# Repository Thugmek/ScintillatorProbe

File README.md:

# Scintillator Gamma Detector

## License

All software in this repository is licensed under [GNU GPLv3](https://choosealicense.com/licenses/gpl-3.0/).
All hardware in this repository is licensed under [CERN OHL v2 Permissive](https://choosealicense.com/licenses/cern-ohl-p-2.0/).

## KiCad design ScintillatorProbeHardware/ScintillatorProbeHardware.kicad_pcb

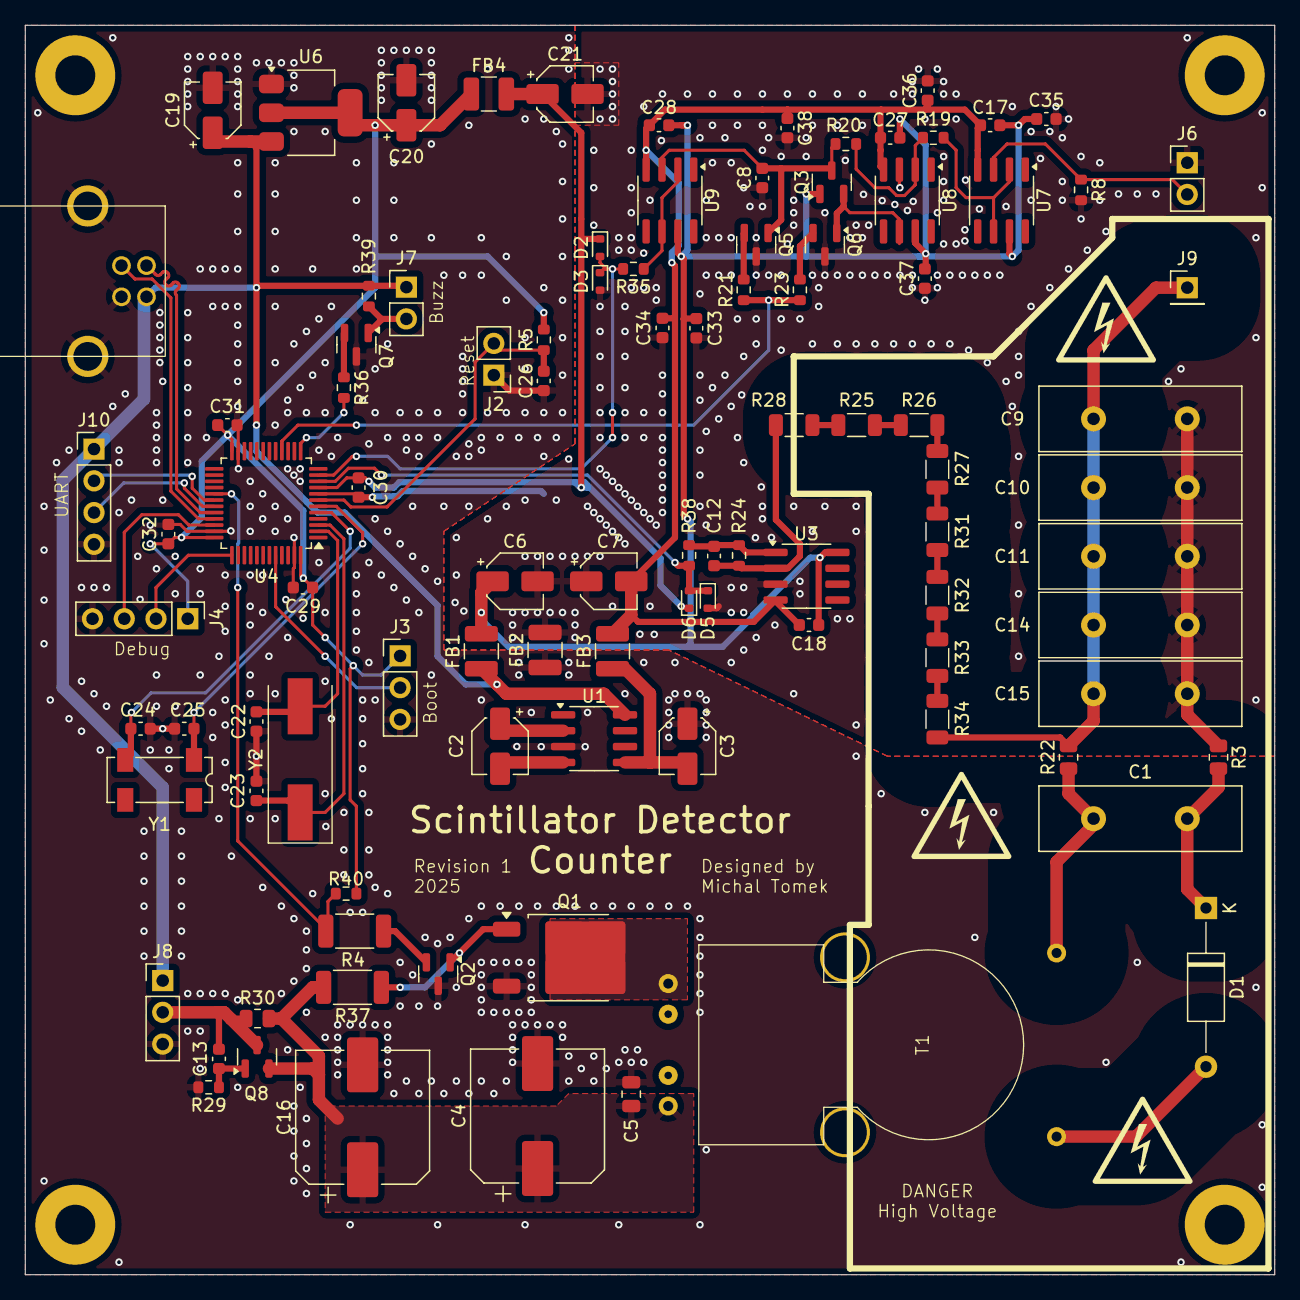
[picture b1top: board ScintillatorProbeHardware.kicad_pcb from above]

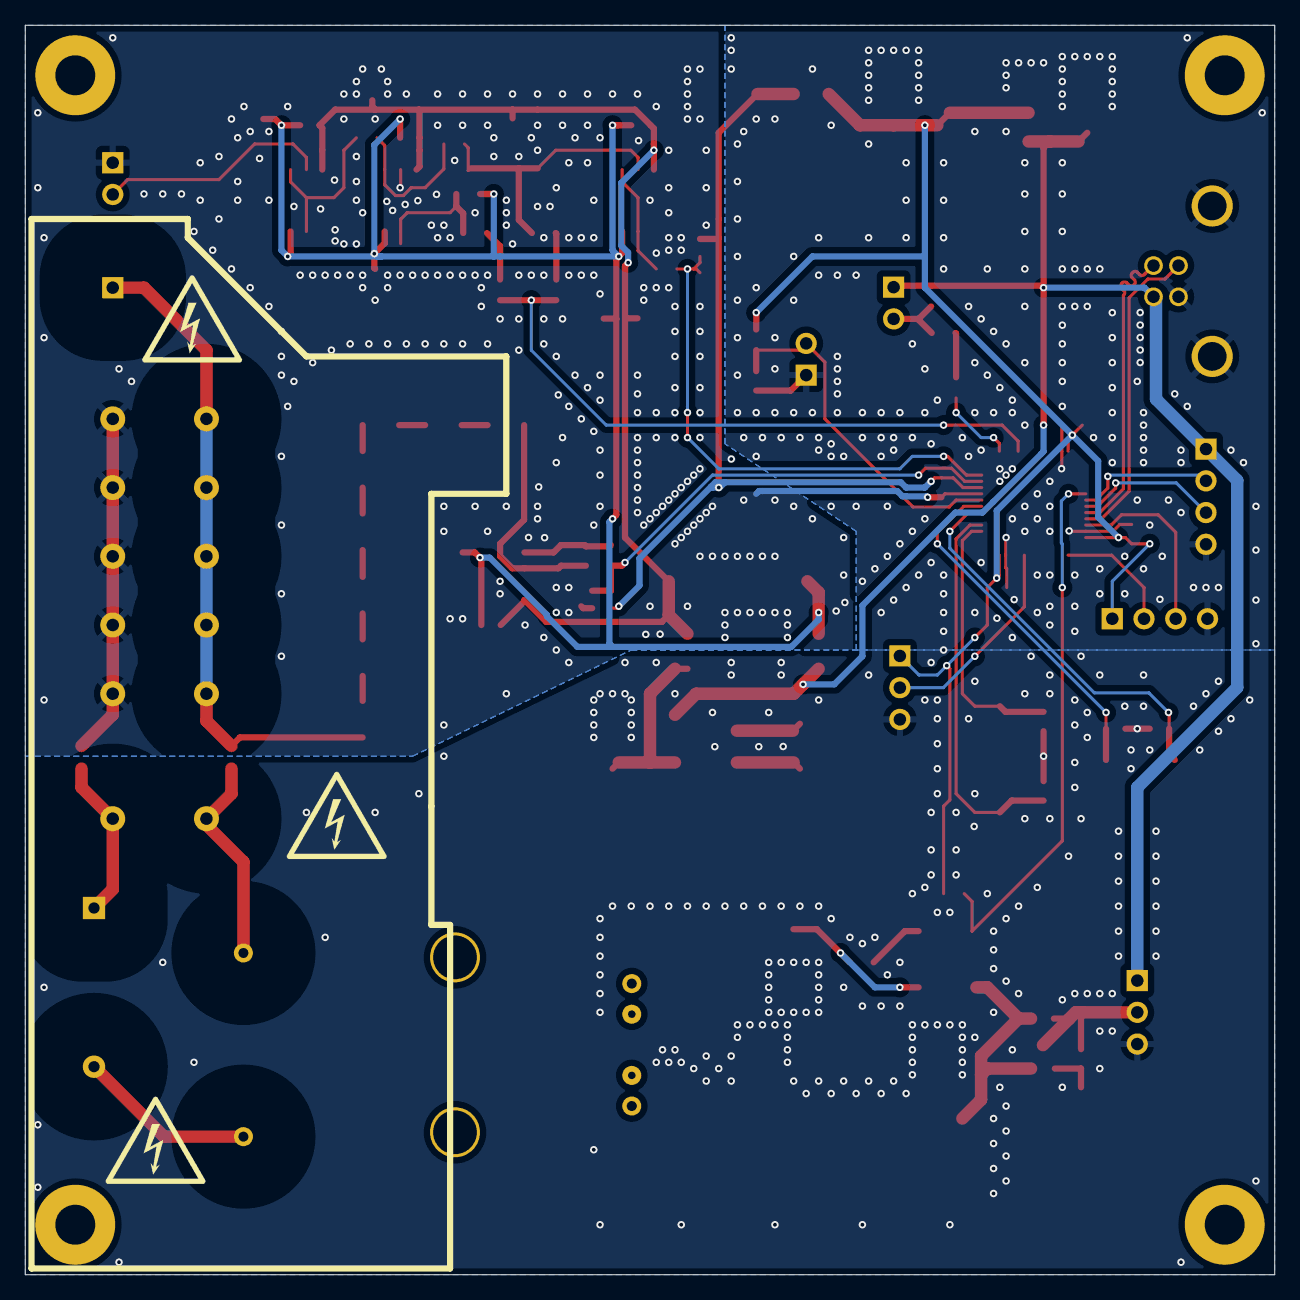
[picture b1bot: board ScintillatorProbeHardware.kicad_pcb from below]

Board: 2 copper layers, 100.0 x 100.0 mm, 109 parts (3 on the bottom side), 56 nets.

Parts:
C1: 10n/3000V; C_Disc_D16.0mm_W5.0mm_P7.50mm
C2, C3, C6, C7, C19, C20, C21: 10u; CP_Elec_4x5.4
C4, C16: 1000u; CP_Elec_10x10.5
C5: 10u; C_0805_2012Metric
C8: 10n; C_0603_1608Metric
C9, C10, C11, C14, C15: 10n; C_Disc_D16.0mm_W5.0mm_P7.50mm
C12, C18, C26: 100n; C_0603_1608Metric
C13, C17, C27, C28, C29, C30, C31, C32, C33, C34, C35, C36, C37, C38: 1u; C_0603_1608Metric
C22, C23, C24, C25: 20p; C_0603_1608Metric
D1: 2CL71A; D_A-405_P12.70mm_Horizontal
D2, D3, D5, D6: D_Schottky; D_SOD-523
FB1, FB2, FB3, FB4: 620Ω@1MHz; L_1210_3225Metric
H1, H2, H3, H4: MountingHole; MountingHole_3.2mm_M3_Pad
J1: USB_B; Amphenol_USB_B
J2, J7: Conn_01x02; PinHeader_1x02_P2.54mm_Vertical
J3, J8: Conn_01x03; PinHeader_1x03_P2.54mm_Vertical
J4, J10: Conn_01x04; PinHeader_1x04_P2.54mm_Vertical
J6: PinHeader_1x02_P2.54mm_Vertical
J9: Conn_01x01; PinHeader_1x01_P2.54mm_Vertical
Q1: 15N10; TO-252-2
Q2, Q3, Q5, Q6, Q7: S8050; SOT-23
Q8: MDD2302; SOT-23
R3, R22: 47k; R_0805_2012Metric
R4, R37: 330R; R_2010_5025Metric
R5, R20: 10k; R_0603_1608Metric
R8, R19, R35, R36, R38, R39, R40: 1k; R_0603_1608Metric
R21, R23: 330R; R_0603_1608Metric
R24: 9k1; R_0603_1608Metric
R25, R26, R27, R28, R31, R32, R33, R34: 1M; R_1206_3216Metric
R29: 100k; R_0603_1608Metric
R30: 47R; R_0805_2012Metric
SYM1, SYM2, SYM3, SYM4, SYM5, SYM6: SYM_Flash_Small; W012 - electricity hazard
T1: 24:1800; 15kV_Transformer
U1: ICL7660; SOIC-8_3.9x4.9mm_P1.27mm
U3: LM358; SOIC-8_3.9x4.9mm_P1.27mm
U4: STM32F103C8Tx; LQFP-48_7x7mm_P0.5mm
U6: AMS1117-3.3; SOT-223-3_TabPin2
U7, U8, U9: LM318N; SOIC-8_3.9x4.9mm_P1.27mm
Y1: 32.768kHz; Crystal_SMD_SeikoEpson_MC306-4Pin_8.0x3.2mm
Y2: 8MHz; Crystal_SMD_HC49-SD

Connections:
+3.3V: C20.1, C29.2, C31.2, C32.2, FB4.1, J3.1, J4.1, R5.2, R40.1, U4.24 (VDD), U4.36 (VDD), U4.48 (VDD), U6.2 (VO)
+3.3VA: C21.1, C30.2, D2.1 (K), D6.1 (K), FB4.2, U4.9 (VDDA)
+5V: C19.1, FB1.1, J1.1 (VBUS), J7.1, J8.1, J10.1, R39.1, U1.8 (V+), U6.3 (VI)
+5VA: C6.1, C17.2, C18.2, C27.2, C28.2, C33.2, C35.2, C37.2, FB1.2, Q3.1 (C), U3.8 (V+), U7.7 (V+), U8.7 (V+), U9.7 (V+)
-5V: C3.2, FB3.1, U1.5 (VOUT)
-5VA: C7.2, C17.1, C18.1, C27.1, C28.1, C34.1, C36.1, C38.1, FB3.2, U3.4 (V-), U7.4 (V-), U8.4 (V-), U9.4 (V-)
BOOT0: J3.2, U4.44 (BOOT0)
Buzzer: R36.2, U4.13 (PA3)
GND: C3.1, C4.2, C5.2, C16.2, C19.2, C20.2, C22.1, C23.1, C24.1, C25.1, C26.1, C29.1, C31.1, C32.1, FB2.1, J1.4 (GND), J1.5 (Shield), J2.1, J3.3, J4.4, J8.3, J10.4, Q1.3 (S), Q2.3 (E), Q7.3 (E), R29.2, U1.3 (GND), U4.23 (VSS), U4.35 (VSS), U4.47 (VSS), U6.1 (GND)
GNDA: C6.2, C7.1, C8.1, C9.2, C10.2, C11.2, C14.2, C15.2, C21.2, C30.1, C33.1, C34.2, C35.1, C36.2, C37.1, C38.2, D3.2 (A), D5.2 (A), FB2.2, J6.1, Q5.3 (E), Q6.3 (E), R3.1, R8.2, U3.3 (+), U4.8 (VSSA), U8.3 (+)
HT: C9.1, C10.1, C11.1, C14.1, C15.1, J9.1, R22.2, R34.2
HT_Drive_Pulse: R4.1, R40.2, U4.29 (PA8)
HT_Power: C13.1, J8.2, Q8.3 (D), R30.1
HT_Sense: D5.1 (K), D6.2 (A), R38.2, U4.10 (PA0)
unnamed: C12.2, R24.1, R38.1, U3.1
unnamed: D1.2 (A), T1.3 (SA)
unnamed: C1.2, D1.1 (K), R3.2
unnamed: C26.2, J2.2, R5.1, U4.7 (NRST)
unnamed: J7.2, Q7.1 (C), R39.2
unnamed: Q1.2 (D), T1.2 (AB)
unnamed: Q1.1 (G), Q2.1 (C), R37.1
unnamed: Q2.2 (B), R4.2
unnamed: Q3.2 (B), Q6.1 (C), U8.6
unnamed: C8.2, Q3.3 (E), Q5.1 (C), R20.2, U9.3 (+)
unnamed: Q5.2 (B), R21.2
unnamed: Q6.2 (B), R23.2
unnamed: Q7.2 (B), R36.1
unnamed: C13.2, Q8.1 (G), R29.1
unnamed: C4.1, C5.1, C16.1, Q8.2 (S), R30.2, R37.2, T1.1 (AA)
unnamed: R25.1, R26.1
unnamed: R25.2, R28.1
unnamed: R26.2, R27.1
unnamed: R27.2, R31.2
unnamed: R31.1, R32.2
unnamed: R32.1, R33.1
unnamed: R33.2, R34.1
unnamed: C1.1, R22.1, T1.4 (SB)
unnamed: C2.1, U1.2 (CAP+)
unnamed: C2.2, U1.4 (CAP-)
unnamed: C12.1, R24.2, R28.2, U3.2 (-)
unnamed: C22.2, U4.2 (PC13), Y2.2
unnamed: C23.2, U4.3 (PC14), Y2.1
unnamed: C24.2, U4.5 (PD0), Y1.2
unnamed: C25.2, U4.6 (PD1), Y1.1
unnamed: R19.1, U7.2 (-), U7.6
unnamed: R19.2, R20.1, U8.2 (-)
unnamed: R35.1, U9.2 (-), U9.6
PMT_Anode: J6.2, R8.1, U7.3 (+)
Peak_Reset: R21.1, R23.1, U4.16 (PA6)
Peak_Sense: D2.2 (A), D3.1 (K), R35.2, U4.11 (PA1)
SWCLK: J4.2, U4.37 (PA14)
SWDIO: J4.3, U4.34 (PA13)
UART_RX: J10.3, U4.31 (PA10)
UART_TX: J10.2, U4.30 (PA9)
USB_D+: J1.3 (D+), U4.33 (PA12)
USB_D-: J1.2 (D-), U4.32 (PA11)

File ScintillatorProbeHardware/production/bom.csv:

Designator,Footprint,Quantity,Value,LCSC Part #
C1,C_Disc_D16.0mm_W5.0mm_P7.50mm,1,10n/3000V,
"C10, C11, C14, C15, C9",C_Disc_D16.0mm_W5.0mm_P7.50mm,5,10n,
"C12, C18, C26",0603,3,100n,C6119867
"C13, C17, C27, C28, C29, C30, C31, C32, C33, C34, C35, C36, C37, C38",0603,14,1u,C15849
"C16, C4",CP_Elec_10x10.5,2,1000u,C5162355
"C19, C2, C20, C21, C3, C6, C7",CP_Elec_4x5.4,7,10u,RVT1V100M0405
"C22, C23, C24, C25",0603,4,20p,C1648
C5,0805,1,10u,C15850 
C8,0603,1,10n,C1525
D1,D_A-405_P12.70mm_Horizontal,1,2CL71A,
"D2, D3, D5, D6",D_SOD-523,4,D_Schottky,C7502702
"FB1, FB2, FB3, FB4",1210,4,620Ω@1MHz,C2661807
J1,Amphenol_USB_B,1,USB_B,
"J10, J4",PinHeader_1x04_P2.54mm_Vertical,2,Conn_01x04,
"J2, J7",PinHeader_1x02_P2.54mm_Vertical,2,Conn_01x02,
"J3, J8",PinHeader_1x03_P2.54mm_Vertical,2,Conn_01x03,
J6,PinHeader_1x02_P2.54mm_Vertical,1,~,
J9,PinHeader_1x01_P2.54mm_Vertical,1,Conn_01x01,
Q1,TO-252-2,1,15N10,C359106
"Q2, Q3, Q5, Q6, Q7",SOT-23,5,S8050,C2146
Q8,SOT-23,1,MDD2302,C427390
"R19, R35, R36, R38, R39, R40, R8",0603,7,1k,C21190
"R20, R5",0603,2,10k,C25804
"R21, R23",0603,2,330R,C23138
"R22, R3",0805,2,47k,C17713
R24,0603,1,9k1,C23260
"R25, R26, R27, R28, R31, R32, R33, R34",1206,8,1M,C2075184
R29,0603,1,100k,0603
R30,0805,1,47R,C17714
"R37, R4",2010,2,330R,C2889850
T1,15kV_Transformer,1,24:1800,
U1,SOIC-8_3.9x4.9mm_P1.27mm,1,ICL7660,C7881
U3,SOIC-8_3.9x4.9mm_P1.27mm,1,LM358,C7950
U4,LQFP-48_7x7mm_P0.5mm,1,STM32F103C8Tx,C8734
U6,SOT-223-3_TabPin2,1,AMS1117-3.3,C347222
"U7, U8, U9",SOIC-8_3.9x4.9mm_P1.27mm,3,LM318N,C1347395
Y1,Crystal_SMD_SeikoEpson_MC306-4Pin_8.0x3.2mm,1,32.768kHz,C16320
Y2,Crystal_SMD_HC49-SD,1,8MHz,C12674

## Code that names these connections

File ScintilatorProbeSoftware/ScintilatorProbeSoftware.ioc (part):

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Mcu.Name=STM32F103C(8-B)Tx
Mcu.Package=LQFP48
Mcu.UserName=STM32F103C8Tx
PA0-WKUP.Signal=ADCx_IN0
PA1.Signal=ADCx_IN1
PA11.Mode=Device
PA11.Signal=USB_DM
PA12.Mode=Device
PA12.Signal=USB_DP
PA13.Mode=Serial_Wire
PA13.Signal=SYS_JTMS-SWDIO
PA14.Mode=Serial_Wire
PA14.Signal=SYS_JTCK-SWCLK
PA3.Signal=S_TIM2_CH4
PA6.Signal=GPIO_Output
PA8.Signal=S_TIM1_CH1
PC14-OSC32_IN.Mode=LSE-External-Oscillator
PC14-OSC32_IN.Signal=RCC_OSC32_IN
PC15-OSC32_OUT.Mode=LSE-External-Oscillator
PC15-OSC32_OUT.Signal=RCC_OSC32_OUT
PD0-OSC_IN.Mode=HSE-External-Oscillator
PD0-OSC_IN.Signal=RCC_OSC_IN
PD1-OSC_OUT.Mode=HSE-External-Oscillator
PD1-OSC_OUT.Signal=RCC_OSC_OUT
RCC.SYSCLKFreq_VALUE=72000000
RCC.SYSCLKSource=RCC_SYSCLKSOURCE_PLLCLK
board=custom

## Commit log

2025-01-17 USB interface working; Command parser; PWM generator
2025-01-18 Voltage read-out
2025-01-19 PID regulator (not tuned)
2025-01-19 some work on controll app
2025-01-20 KiCad .gitignore
2025-01-20 Flyback driving circuit changed to NMOS
2025-01-20 Controll app PID page started
2025-01-21 Debug voltages and PWM
2025-01-21 Voltage read-out chart
2025-01-21 Controllable PWM form App
2025-01-24 Added some LCSC numbers
2025-01-27 Removed research materials
2025-01-27 Spectrum read-out
2025-01-27 compilation error fixes
2025-01-31 Measurement decimation implemented
2025-02-02 Peak detector circuit simulation
2025-02-22 added transformer model; experiments with beeping code
2025-02-23 PCB layout started, firmware modified for new peak detector
2025-02-23 Pulse beeping; minor fixes
2025-02-28 PCB mostly routed
2025-02-28 Added USB connector, some loops on PCB optimized
2025-02-28 Hardware finisnig touches, Software directory typo fixed
2025-03-01 License added
2025-03-03 Hardware revision 1 as sent to manifacture
2025-10-31 new kicad project
2025-11-02 some work
